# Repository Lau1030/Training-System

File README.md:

# Training-System
Un sistema conformado por un sensor MAX30102 que estará conectado a un ESP32 el cual a través de ESP-NOW, (que es un protocolo inalámbrico de comunicación directa desarrollado por Espressif Systems para sus microcontroladores) se comunicara con otro ESP32 el cual pasara los datos recibidos a un Display LCD para que el usuario pueda visualizar su ritmo cardiaco.

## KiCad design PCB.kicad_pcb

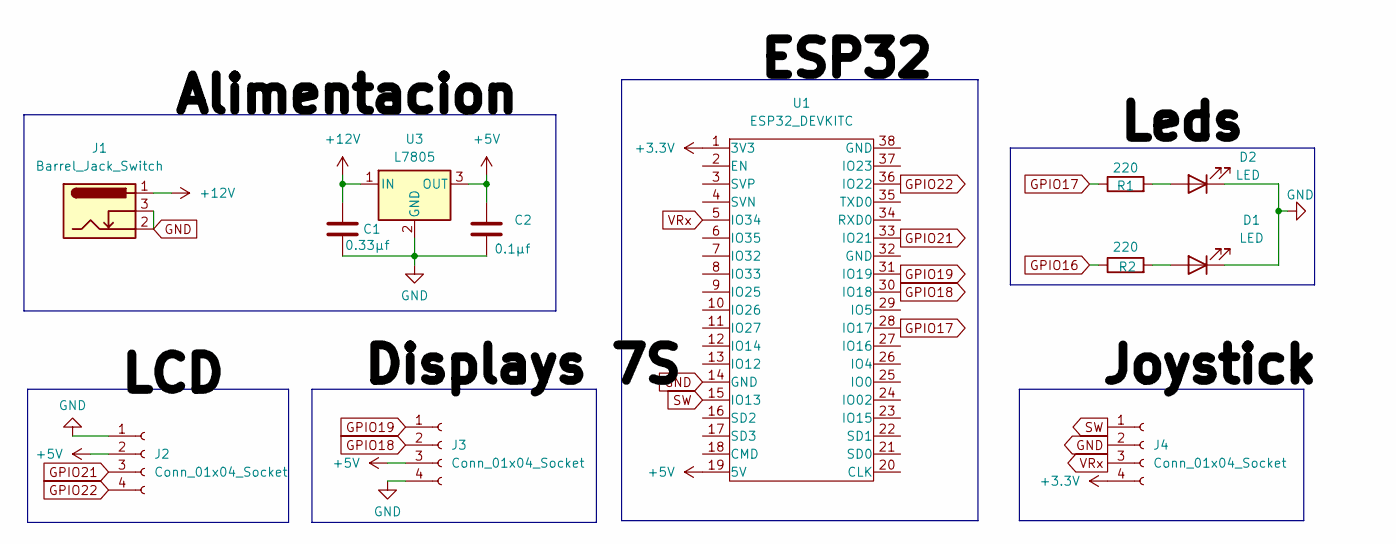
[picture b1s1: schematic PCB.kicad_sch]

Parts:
C1: 0.33µf; C_0805_2012Metric
C2: 0.1µf; C_0805_2012Metric
D1, D2: LED; led_5mm_red
J1: Barrel_Jack_Switch; BarrelJack_Horizontal
J2, J3, J4: Conn_01x04_Socket; PinSocket_1x04_P2.00mm_Vertical
R1, R2: 220; R_0805
U1: ESP32_DEVKITC; ESP32S
U3: L7805; TO-263-3_TabPin2

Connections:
+3.3V: J4.4, U1.1 (3V3)
+5V: C2.1, J2.2, J3.3, U1.19 (5V), U3.3 (OUT)
+12V: C1.1, J1.1, U3.1 (IN)
GND: C1.2, C2.2, D1.1 (K), D2.1 (K), J1.2, J1.3, J2.1, J3.4, J4.2, U1.14 (GND), U3.2 (GND)
GPIO16: R2.1
GPIO17: R1.1, U1.28 (IO17)
GPIO18: J3.2, U1.30 (IO18)
GPIO19: J3.1, U1.31 (IO19)
GPIO21: J2.3, U1.33 (IO21)
GPIO22: J2.4, U1.36 (IO22)
unnamed: D1.2 (A), R2.2
unnamed: D2.2 (A), R1.2
SW: J4.1, U1.15 (IO13)
VRx: J4.3, U1.5 (IO34)

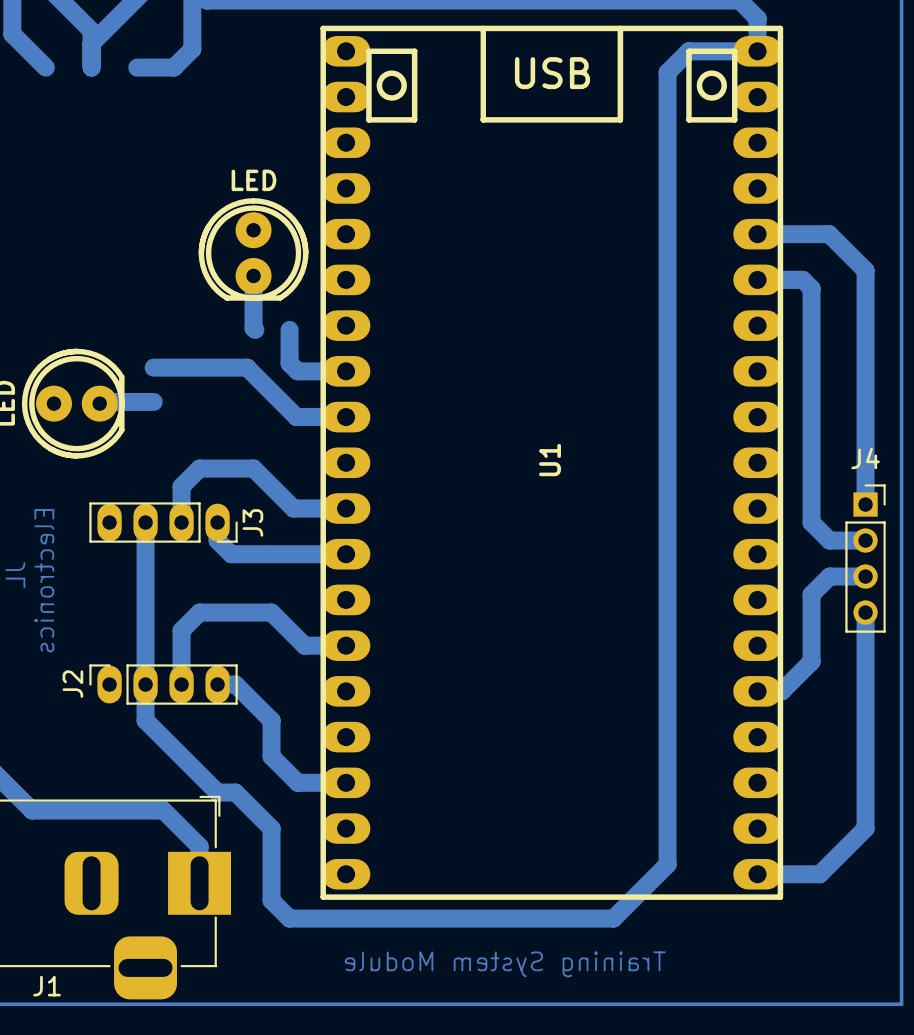
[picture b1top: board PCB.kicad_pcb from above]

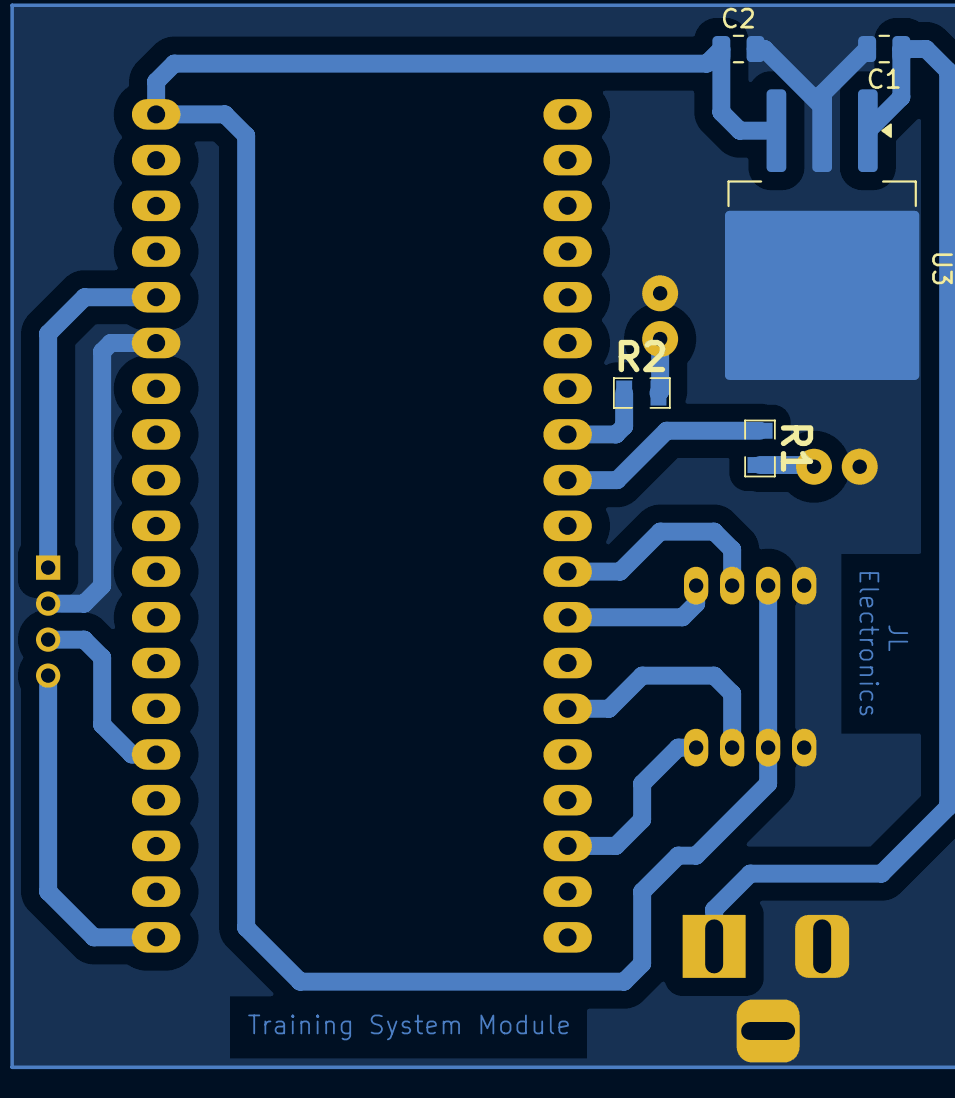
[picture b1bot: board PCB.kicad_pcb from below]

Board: 2 copper layers, 12 parts (5 on the bottom side), 13 nets.

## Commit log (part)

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2026-06-19 Update communication protocol description in README
2026-06-19 Add brief description of the training system
